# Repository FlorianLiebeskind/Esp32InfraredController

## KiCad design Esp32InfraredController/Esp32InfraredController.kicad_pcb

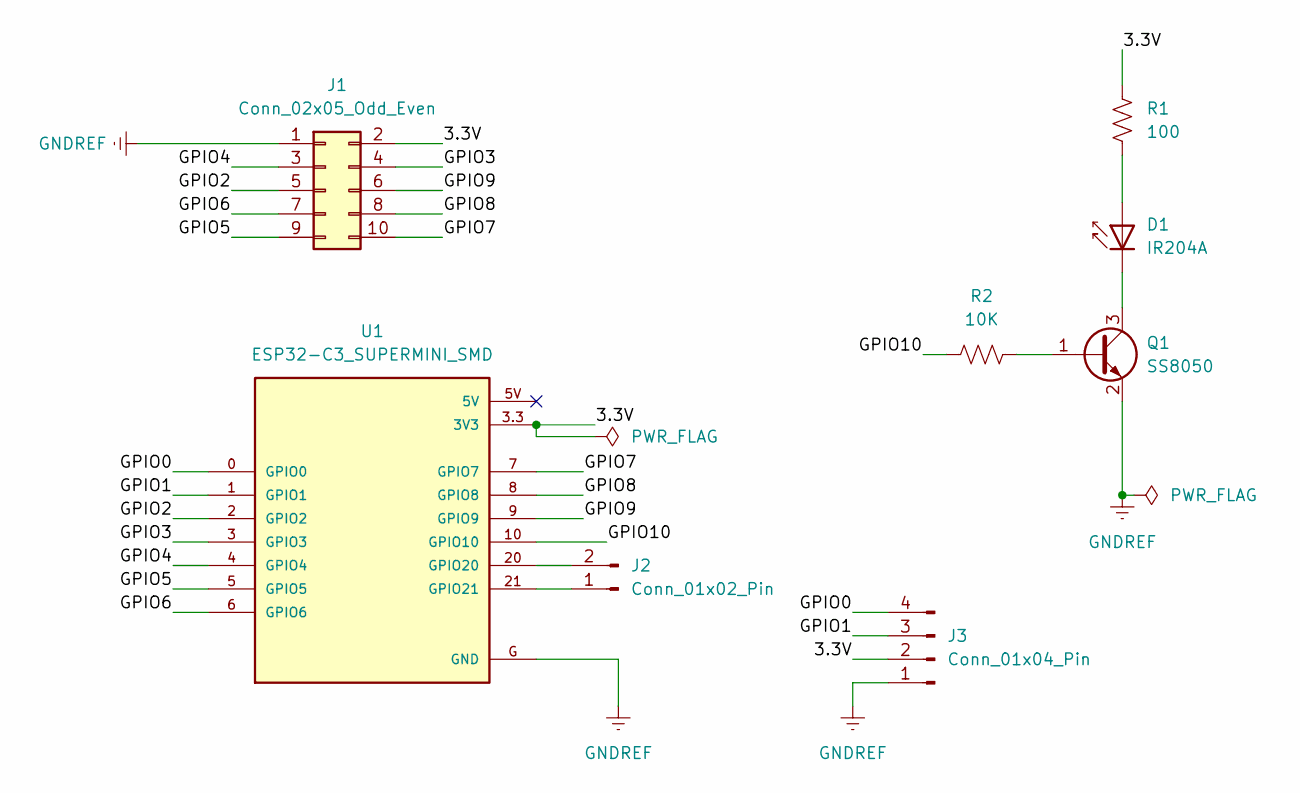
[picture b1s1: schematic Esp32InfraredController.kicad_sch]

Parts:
D1: IR204A; LED_D3.0mm_IRBlack
J1: Conn_02x05_Odd_Even; PinSocket_2x05_P2.54mm_Vertical_SMD
J2: Conn_01x02_Pin; PinHeader_1x02_P1.00mm_Vertical
J3: Conn_01x04_Pin; PinHeader_1x04_P1.00mm_Vertical
Q1: SS8050; SOT-23
R1: 100; R_0603_1608Metric
R2: 10K; R_0603_1608Metric
U1: ESP32-C3_SUPERMINI_SMD; MODULE_ESP32-C3_SUPERMINI

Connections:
/3.3V: J1.2, J3.2, R1.1, U1.3.3 (3V3)
/GPIO0: J3.4, U1.0 (GPIO0)
/GPIO1: J3.3, U1.1 (GPIO1)
/GPIO2: J1.5, U1.2 (GPIO2)
/GPIO3: J1.4, U1.3 (GPIO3)
/GPIO4: J1.3, U1.4 (GPIO4)
/GPIO5: J1.9, U1.5 (GPIO5)
/GPIO6: J1.7, U1.6 (GPIO6)
/GPIO7: J1.10, U1.7 (GPIO7)
/GPIO8: J1.8, U1.8 (GPIO8)
/GPIO9: J1.6, U1.9 (GPIO9)
/GPIO10: R2.1, U1.10 (GPIO10)
GNDREF: J1.1, J3.1, Q1.2 (E), U1.G (GND)
unnamed: D1.2 (A), R1.2
unnamed: D1.1 (K), Q1.3 (C)
unnamed: J2.1, U1.21 (GPIO21)
unnamed: J2.2, U1.20 (GPIO20)
unnamed: Q1.1 (B), R2.2

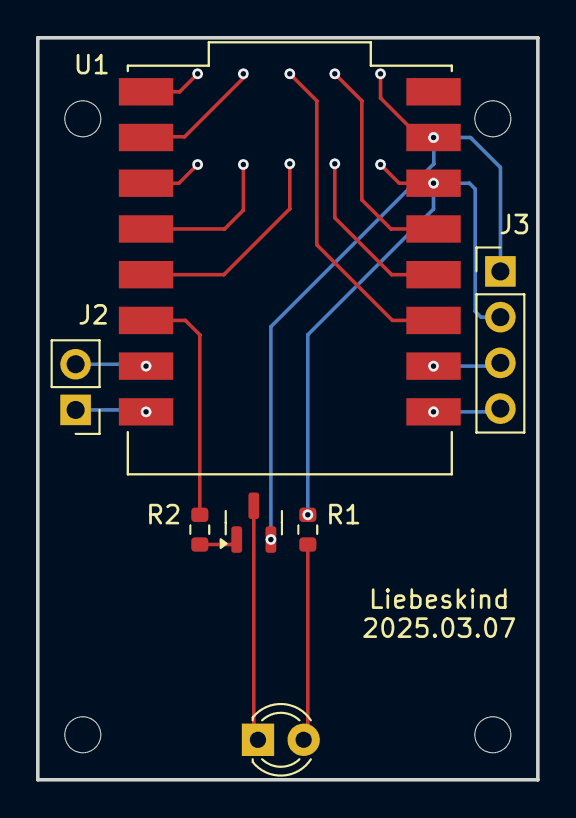
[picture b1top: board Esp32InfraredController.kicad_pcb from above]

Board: 2 copper layers, 27.8 x 41.2 mm, 8 parts (1 on the bottom side), 18 nets.

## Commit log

2025-03-05 添加“1.3寸ips 240X240TFT显示屏高清液晶1.3寸st7789 ips显示屏”
2025-03-05 no message
